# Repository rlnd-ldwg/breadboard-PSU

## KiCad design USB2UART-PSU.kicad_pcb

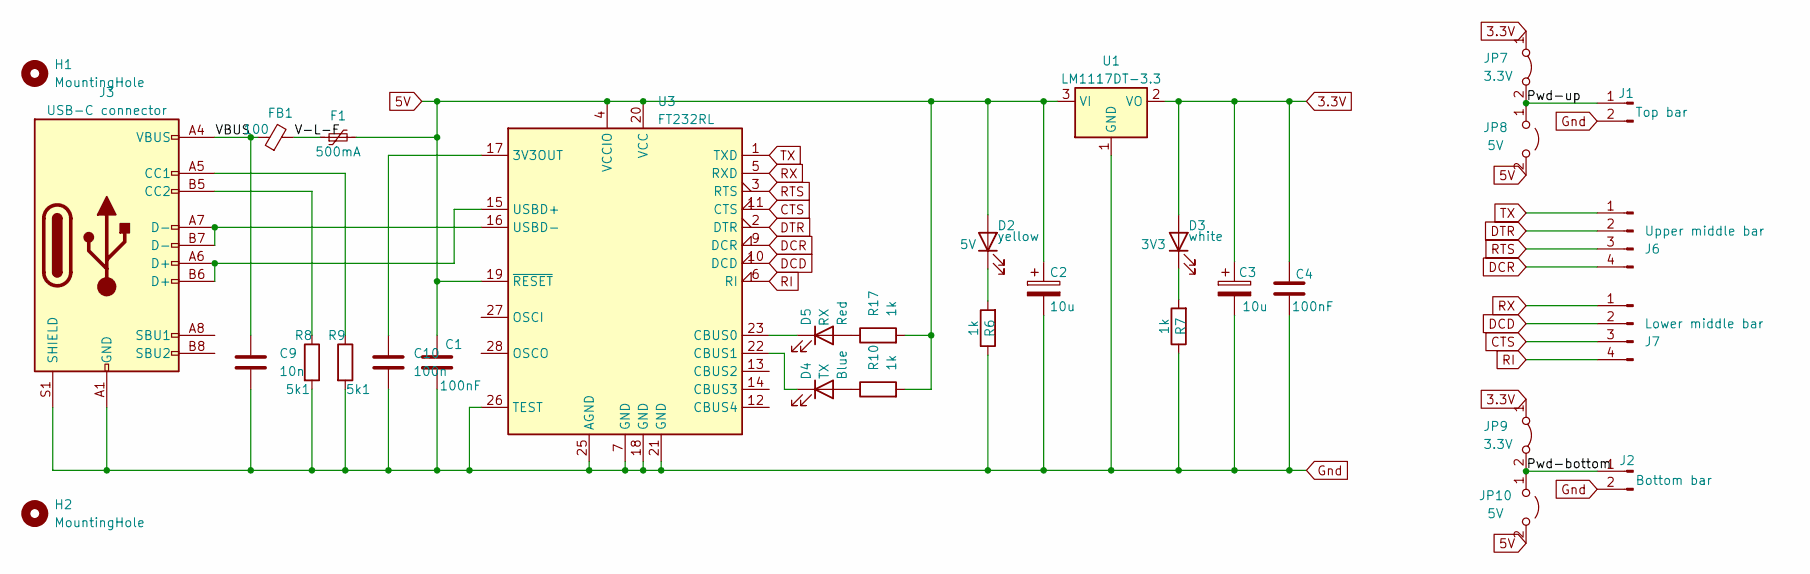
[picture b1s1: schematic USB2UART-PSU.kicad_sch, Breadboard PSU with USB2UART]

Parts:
C1, C4: 100nF; C_1206_3216Metric_Pad1.33x1.80mm_HandSolder
C2, C3: 10u; C_1206_3216Metric_Pad1.33x1.80mm_HandSolder
C9: 10n; C_1206_3216Metric_Pad1.33x1.80mm_HandSolder
C10: 100n; C_1206_3216Metric_Pad1.33x1.80mm_HandSolder
D2: yellow; D_1206_3216Metric_Pad1.42x1.75mm_HandSolder
D3: white; D_1206_3216Metric_Pad1.42x1.75mm_HandSolder
D4: Blue; D_1206_3216Metric_Pad1.42x1.75mm_HandSolder
D5: Red; D_1206_3216Metric_Pad1.42x1.75mm_HandSolder
F1: 500mA; Fuse_1206_3216Metric_Pad1.42x1.75mm_HandSolder
FB1: 100; L_1206_3216Metric_Pad1.22x1.90mm_HandSolder
H1, H2: MountingHole; MountingHole_3.2mm_M3_ISO14580_Pad_TopBottom
J1: Top bar; PinHeader_1x02_P2.54mm_Vertical
J2: Bottom bar; PinHeader_1x02_P2.54mm_Vertical
J3: USB-C connector; USB-C_Core-Set
J6: Upper middle bar; PinHeader_1x04_P2.54mm_Vertical
J7: Lower middle bar; PinHeader_1x04_P2.54mm_Vertical
JP7, JP9: 3.3V; PinHeader_1x02_P1.27mm_Vertical
JP8, JP10: 5V; PinHeader_1x02_P1.27mm_Vertical
R6, R7, R10, R17: 1k; R_1206_3216Metric_Pad1.30x1.75mm_HandSolder
R8, R9: 5k1; R_1206_3216Metric_Pad1.30x1.75mm_HandSolder
U1: LM1117DT-3.3; SOT-223-3_TabPin2
U3: FT232RL; SSOP-28_5.3x10.2mm_P0.65mm

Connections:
3.3V: C3.1, C4.1, D3.2 (A), JP7.1 (A), JP9.1 (A), U1.2 (VO)
5V: C1.1, C2.1, D2.2 (A), F1.2, JP8.2 (B), JP10.2 (B), R10.2, R17.2, U1.3 (VI), U3.4 (VCCIO), U3.19 (~RESET), U3.20 (VCC)
/Pwd-bottom: J2.1, JP9.2 (B), JP10.1 (A)
/Pwd-up: J1.1, JP7.2 (B), JP8.1 (A)
/V-L-F: F1.1, FB1.2
/VBUS: C9.1, FB1.1, J3.A4 (VBUS), J3.A9 (VBUS), J3.B4 (VBUS), J3.B9 (VBUS)
CTS: J7.3, U3.11 (CTS)
DCD: J7.2, U3.10 (DCD)
DCR: J6.4, U3.9 (DCR)
DTR: J6.2, U3.2 (DTR)
Gnd: C1.2, C2.2, C3.2, C4.2, C9.2, C10.2, J1.2, J2.2, J3.A1 (GND), J3.A12 (GND), J3.B1 (GND), J3.B12 (GND), J3.S1 (SHIELD), R6.1, R7.1, R8.2, R9.2, U1.1 (GND), U3.7 (GND), U3.18 (GND), U3.21 (GND), U3.25 (AGND), U3.26 (TEST)
unnamed: D2.1 (K), R6.2
unnamed: D3.1 (K), R7.2
unnamed: D4.2 (A), R10.1
unnamed: D4.1 (K), U3.22 (CBUS1)
unnamed: D5.2 (A), R17.1
unnamed: D5.1 (K), U3.23 (CBUS0)
unnamed: J3.A5 (CC1), R9.1
unnamed: J3.B5 (CC2), R8.1
unnamed: C10.1, U3.17 (3V3OUT)
unnamed: J3.A6 (D+), J3.B6 (D+), U3.15 (USBD+)
unnamed: J3.A7 (D-), J3.B7 (D-), U3.16 (USBD-)
RI: J7.4, U3.6 (RI)
RTS: J6.3, U3.3 (RTS)
RX: J7.1, U3.5 (RXD)
TX: J6.1, U3.1 (TXD)

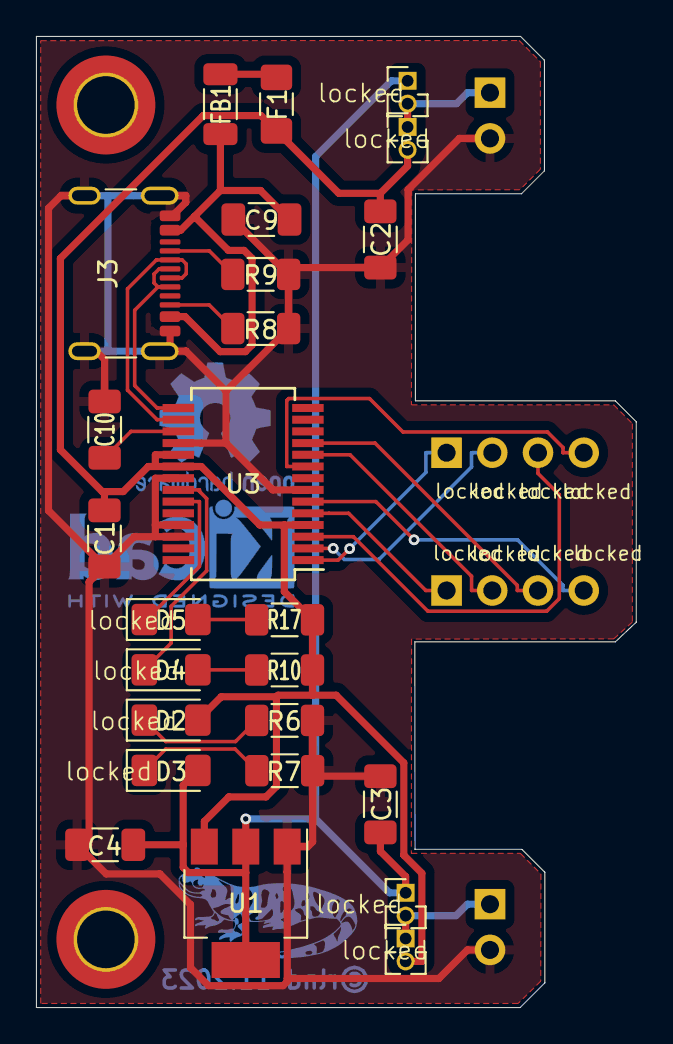
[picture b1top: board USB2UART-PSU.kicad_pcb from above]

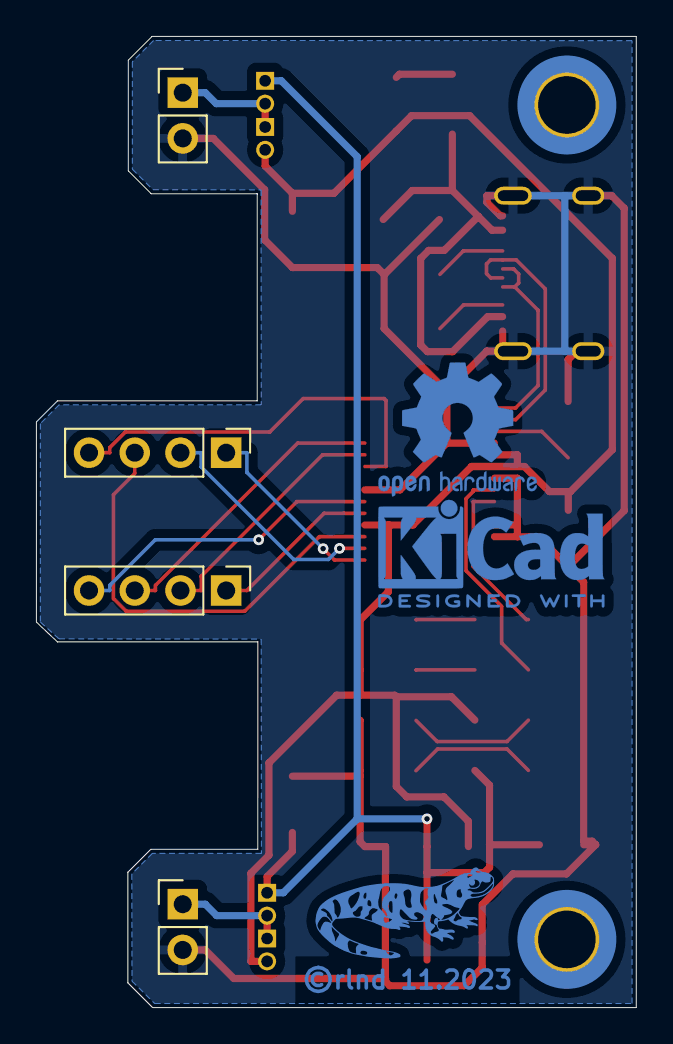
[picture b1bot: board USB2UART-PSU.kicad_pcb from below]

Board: 2 copper layers, 33.3 x 53.9 mm, 31 parts (4 on the bottom side), 26 nets.

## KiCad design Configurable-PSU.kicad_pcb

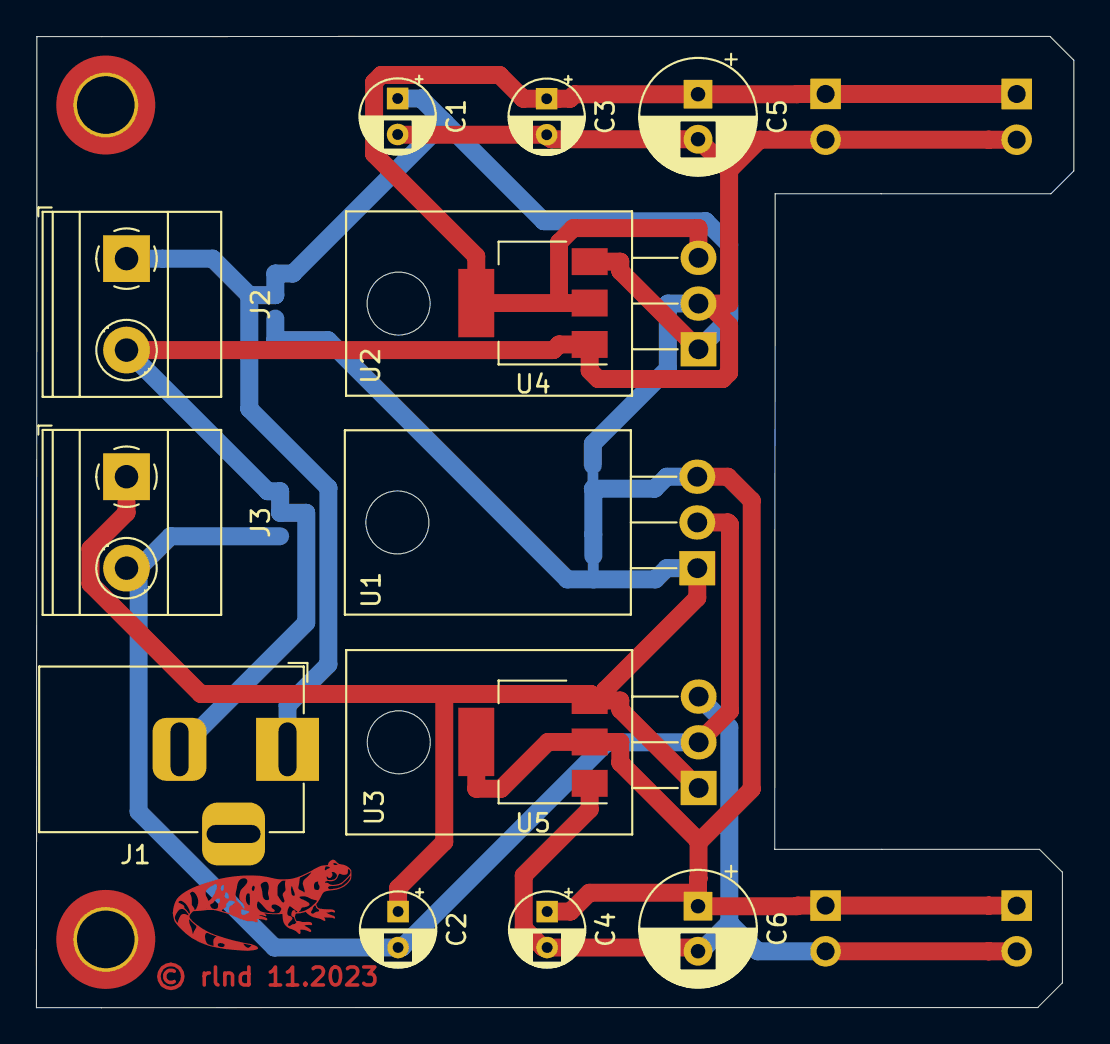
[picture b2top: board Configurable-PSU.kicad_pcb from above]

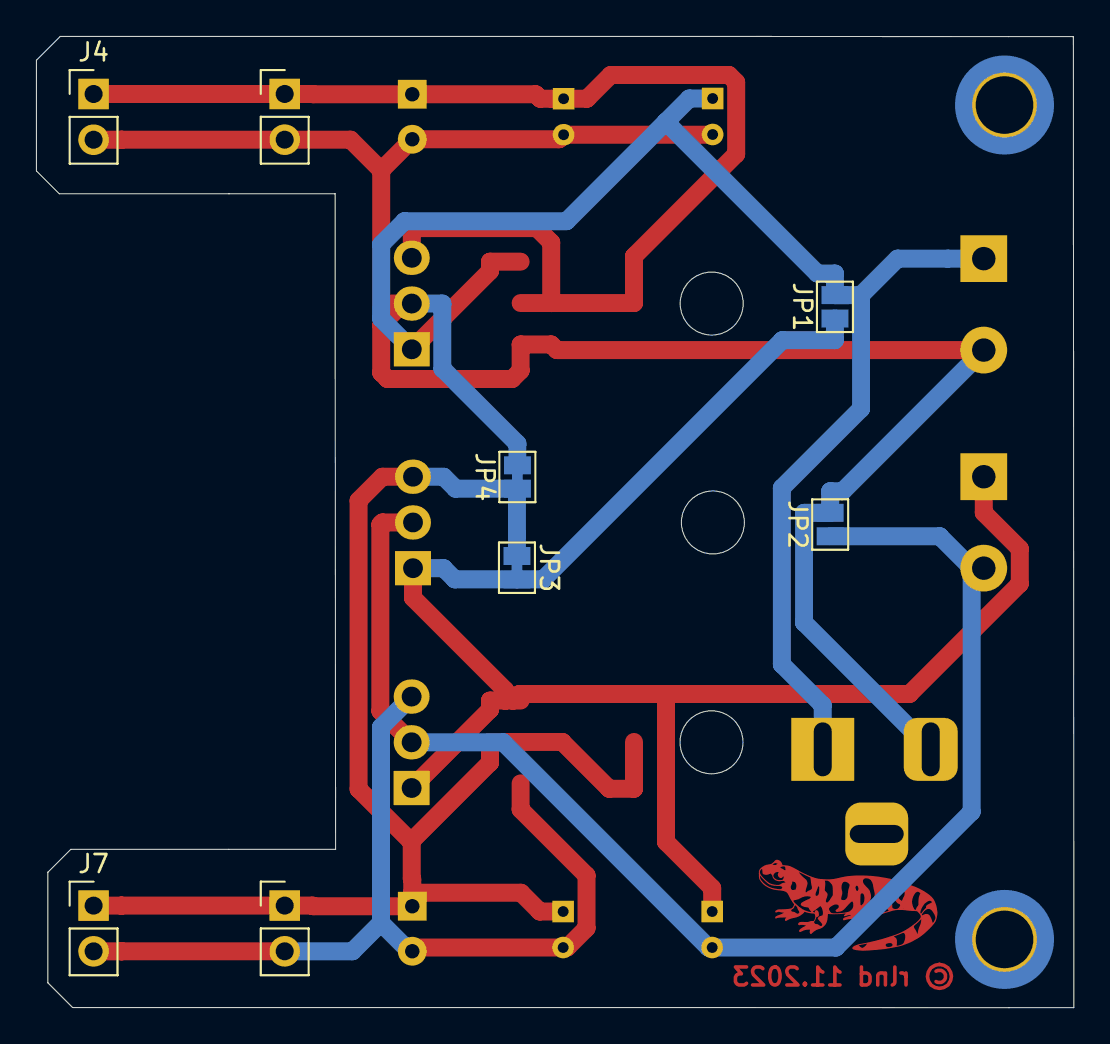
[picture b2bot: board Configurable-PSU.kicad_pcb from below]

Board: 2 copper layers, 57.6 x 54.0 mm, 24 parts (8 on the bottom side), 7 nets.

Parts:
C1, C2: 330n; CP_Radial_D4.0mm_P2.00mm
C3, C4: 100n; CP_Radial_D4.0mm_P2.00mm
C5, C6: 10u; CP_Radial_D6.3mm_P2.50mm
H1, H2: MountingHole; MountingHole_3.2mm_M3_ISO14580_Pad_TopBottom
J1: 12V; BarrelJack_Horizontal
J2, J3: 12V; TerminalBlock_Phoenix_MKDS-1,5-2-5.08_1x02_P5.08mm_Horizont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
J4, J5: Top bar; PinHeader_1x02_P2.54mm_Vertical
J6, J7: Bottom bar; PinHeader_1x02_P2.54mm_Vertical
JP1, JP2: SolderJumper_2_Open; SolderJumper-2_P1.3mm_Open_Pad1.0x1.5mm
JP3, JP4: SolderJumper_2_Bridged; SolderJumper-2_P1.3mm_Bridged_Pad1.0x1.5mm
U1: LM7812_TO220; TO-220-3_Horizontal_TabDown
U2: LM7805_TO220; TO-220-3_Horizontal_TabDown
U3: LM7912_TO220; TO-220-3_Horizontal_TabDown
U4, U5: LM1117DT-5.0; SOT-223-3_TabPin2

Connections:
/Gnd: C4.1, C6.1, J6.1, J7.1, JP3.1 (A), JP4.1 (A), U1.3 (VO), U5.2 (VO)
/Gnd1: C1.2, C3.2, C5.2, J1.2, J2.2, J4.2, J5.2, JP2.2 (B), JP4.2 (B), U2.2 (GND), U4.1 (GND)
/Gnd2: C2.2, J3.2, JP2.1 (A), U1.2 (GND), U3.2 (VI)
/Vcc1: C1.1, J1.1, J2.1, JP1.2 (B), U2.1 (VI), U4.3 (VI)
/Vcc2: C2.1, J3.1, JP1.1 (A), JP3.2 (B), U1.1 (VI), U3.1 (GND), U5.3 (VI)
/Vout1: C3.1, C5.1, J4.1, J5.1, U2.3 (VO), U4.2 (VO)
/Vout2: C4.2, C6.2, J6.2, J7.2, U3.3 (VO), U5.1 (GND)

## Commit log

2024-07-13 .gitignore added

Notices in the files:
Configurable-PSU.kicad_pcb:
© rlnd 11.2023
